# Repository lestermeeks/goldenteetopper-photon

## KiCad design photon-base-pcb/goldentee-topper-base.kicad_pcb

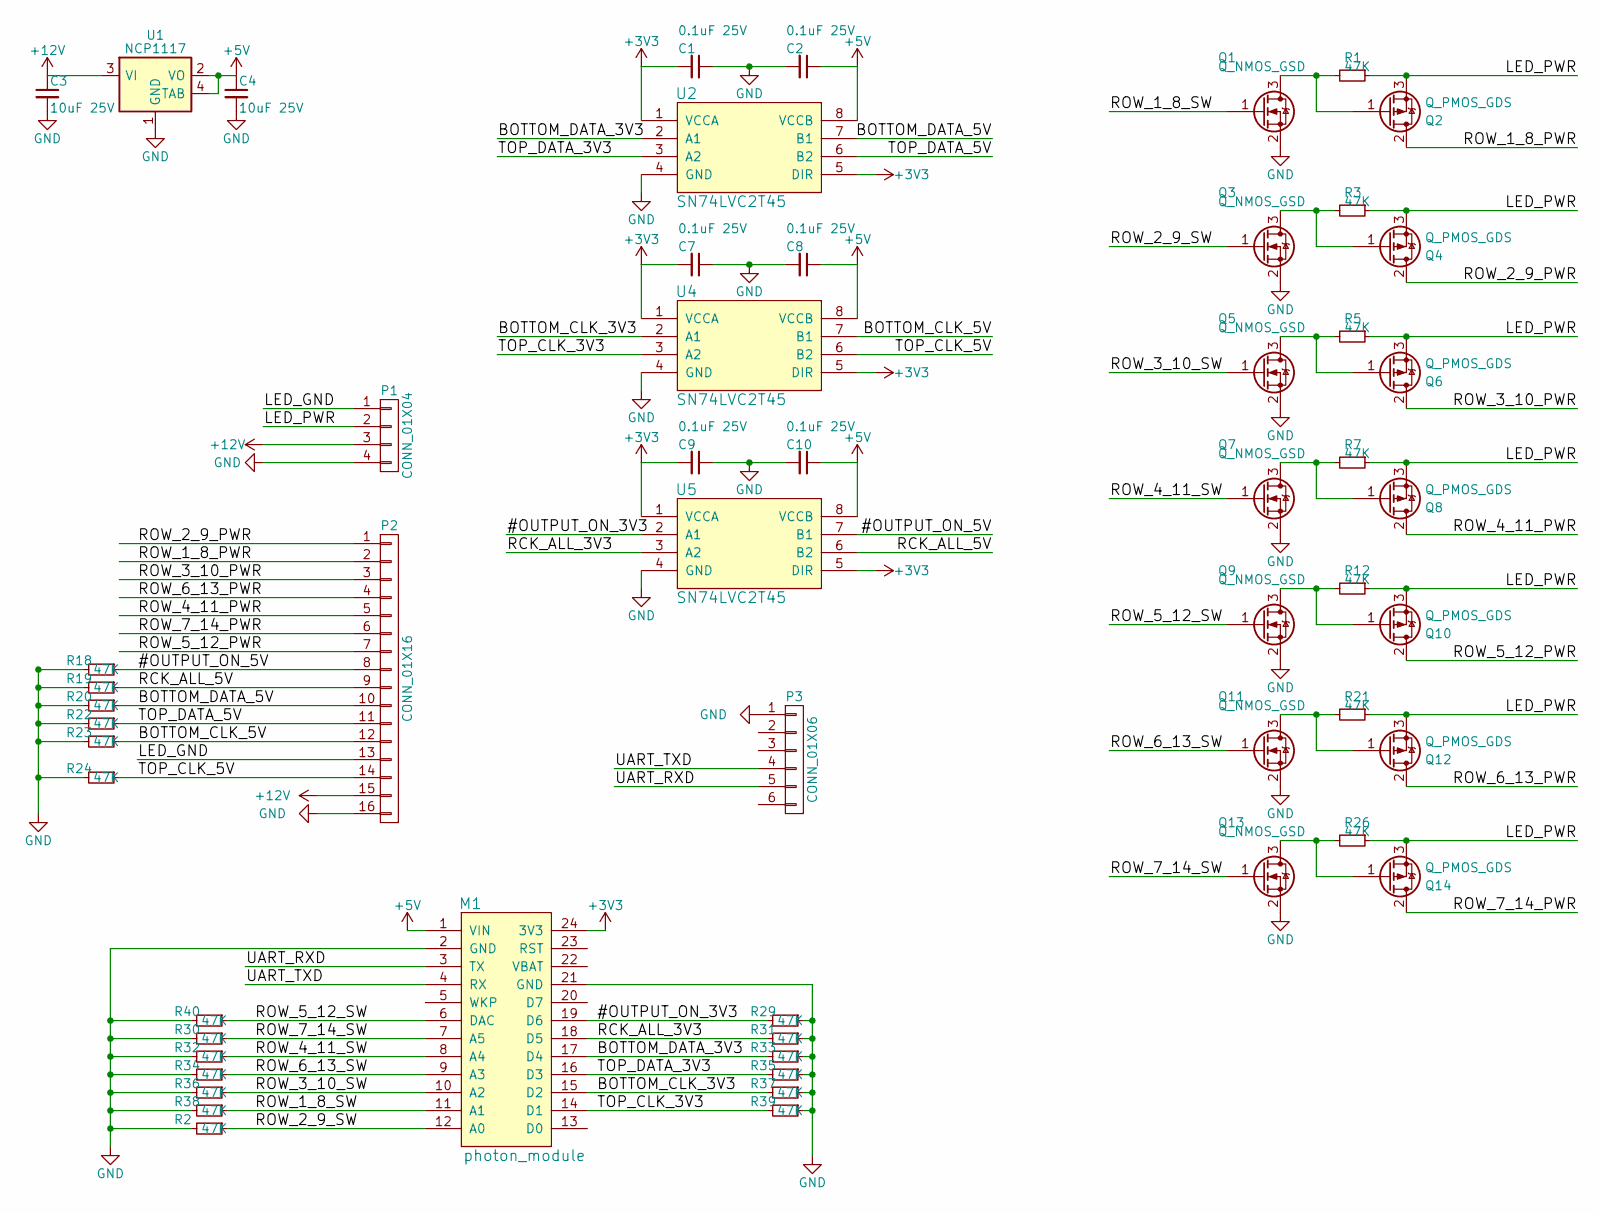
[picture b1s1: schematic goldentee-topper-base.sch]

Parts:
C1, C2, C7, C8, C9, C10: 0.1uF 25V; C_0805_HandSoldering
C3, C4: 10uF 25V; C_1210_HandSoldering
M1: photon_module; photon
P1: CONN_01X04; CONN_0.156
P2: CONN_01X16; CONN_1x16_0.156
P3: CONN_01X06; Pin_Header_Straight_1x06_Pitch2.54mm
Q1, Q3, Q5, Q7, Q9, Q11, Q13: Q_NMOS_GSD; SOT-23_Handsoldering
Q2, Q4, Q6, Q8, Q10, Q12, Q14: Q_PMOS_GDS; TO-252-2Lead
R1, R2, R3, R5, R7, R12, R18, R19, R20, R21, R22, R23, R24, R26, R29, R30, R31, R32, R33, R34, R35, R36, R37, R38, R39, R40: 47K; R_0603_HandSoldering
U1: NCP1117; SOT-223
U2, U4, U5: SN74LVC2T45; SN74LVC2T45DCTR

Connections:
+3V3: C1.2, C7.2, C9.2, M1.24 (3V3), U2.1 (VCCA), U2.5 (DIR), U4.1 (VCCA), U4.5 (DIR), U5.1 (VCCA), U5.5 (DIR)
+5V: C2.1, C4.1, C8.1, C10.1, M1.1 (VIN), U1.2 (VO), U1.4 (TAB), U2.8 (VCCB), U4.8 (VCCB), U5.8 (VCCB)
+12V: C3.1, P1.3, P2.15, U1.3 (VI)
/#OUTPUT_ON_3V3: M1.19 (D6), R29.2, U5.2 (A1)
/#OUTPUT_ON_5V: P2.8, R18.1, U5.7 (B1)
/BOTTOM_CLK_3V3: M1.15 (D2), R37.2, U4.2 (A1)
/BOTTOM_CLK_5V: P2.12, R23.1, U4.7 (B1)
/BOTTOM_DATA_3V3: M1.17 (D4), R33.2, U2.2 (A1)
/BOTTOM_DATA_5V: P2.10, R20.1, U2.7 (B1)
/LED_GND: P1.1, P2.13
/LED_PWR: P1.2, Q2.3 (S), Q4.3 (S), Q6.3 (S), Q8.3 (S), Q10.3 (S), Q12.3 (S), Q14.3 (S), R1.1, R3.1, R5.1, R7.1, R12.1, R21.1, R26.1
/RCK_ALL_3V3: M1.18 (D5), R31.2, U5.3 (A2)
/RCK_ALL_5V: P2.9, R19.1, U5.6 (B2)
/ROW_1_8_PWR: P2.2, Q2.2 (D)
/ROW_1_8_SW: M1.11 (A1), Q1.1 (G), R38.1
/ROW_2_9_PWR: P2.1, Q4.2 (D)
/ROW_2_9_SW: M1.12 (A0), Q3.1 (G), R2.1
/ROW_3_10_PWR: P2.3, Q6.2 (D)
/ROW_3_10_SW: M1.10 (A2), Q5.1 (G), R36.1
/ROW_4_11_PWR: P2.5, Q8.2 (D)
/ROW_4_11_SW: M1.8 (A4), Q7.1 (G), R32.1
/ROW_5_12_PWR: P2.7, Q10.2 (D)
/ROW_5_12_SW: M1.6 (DAC), Q9.1 (G), R40.1
/ROW_6_13_PWR: P2.4, Q12.2 (D)
/ROW_6_13_SW: M1.9 (A3), Q11.1 (G), R34.1
/ROW_7_14_PWR: P2.6, Q14.2 (D)
/ROW_7_14_SW: M1.7 (A5), Q13.1 (G), R30.1
/TOP_CLK_3V3: M1.14 (D1), R39.2, U4.3 (A2)
/TOP_CLK_5V: P2.14, R24.1, U4.6 (B2)
/TOP_DATA_3V3: M1.16 (D3), R35.2, U2.3 (A2)
/TOP_DATA_5V: P2.11, R22.1, U2.6 (B2)
/UART_RXD: M1.3 (TX), P3.5
/UART_TXD: M1.4 (RX), P3.4
GND: C1.1, C2.2, C3.2, C4.2, C7.1, C8.2, C9.1, C10.2, M1.2 (GND), M1.21 (GND), P1.4, P2.16, P3.1, Q1.2 (S), Q3.2 (S), Q5.2 (S), Q7.2 (S), Q9.2 (S), Q11.2 (S), Q13.2 (S), R2.2, R18.2, R19.2, R20.2, R22.2, R23.2, R24.2, R29.1, R30.2, R31.1, R32.2, R33.1, R34.2, R35.1, R36.2, R37.1, R38.2, R39.1, R40.2, U1.1 (GND), U2.4 (GND), U4.4 (GND), U5.4 (GND)
unnamed: Q1.3 (D), Q2.1 (G), R1.2
unnamed: Q3.3 (D), Q4.1 (G), R3.2
unnamed: Q5.3 (D), Q6.1 (G), R5.2
unnamed: Q7.3 (D), Q8.1 (G), R7.2
unnamed: Q9.3 (D), Q10.1 (G), R12.2
unnamed: Q11.3 (D), Q12.1 (G), R21.2
unnamed: Q13.3 (D), Q14.1 (G), R26.2

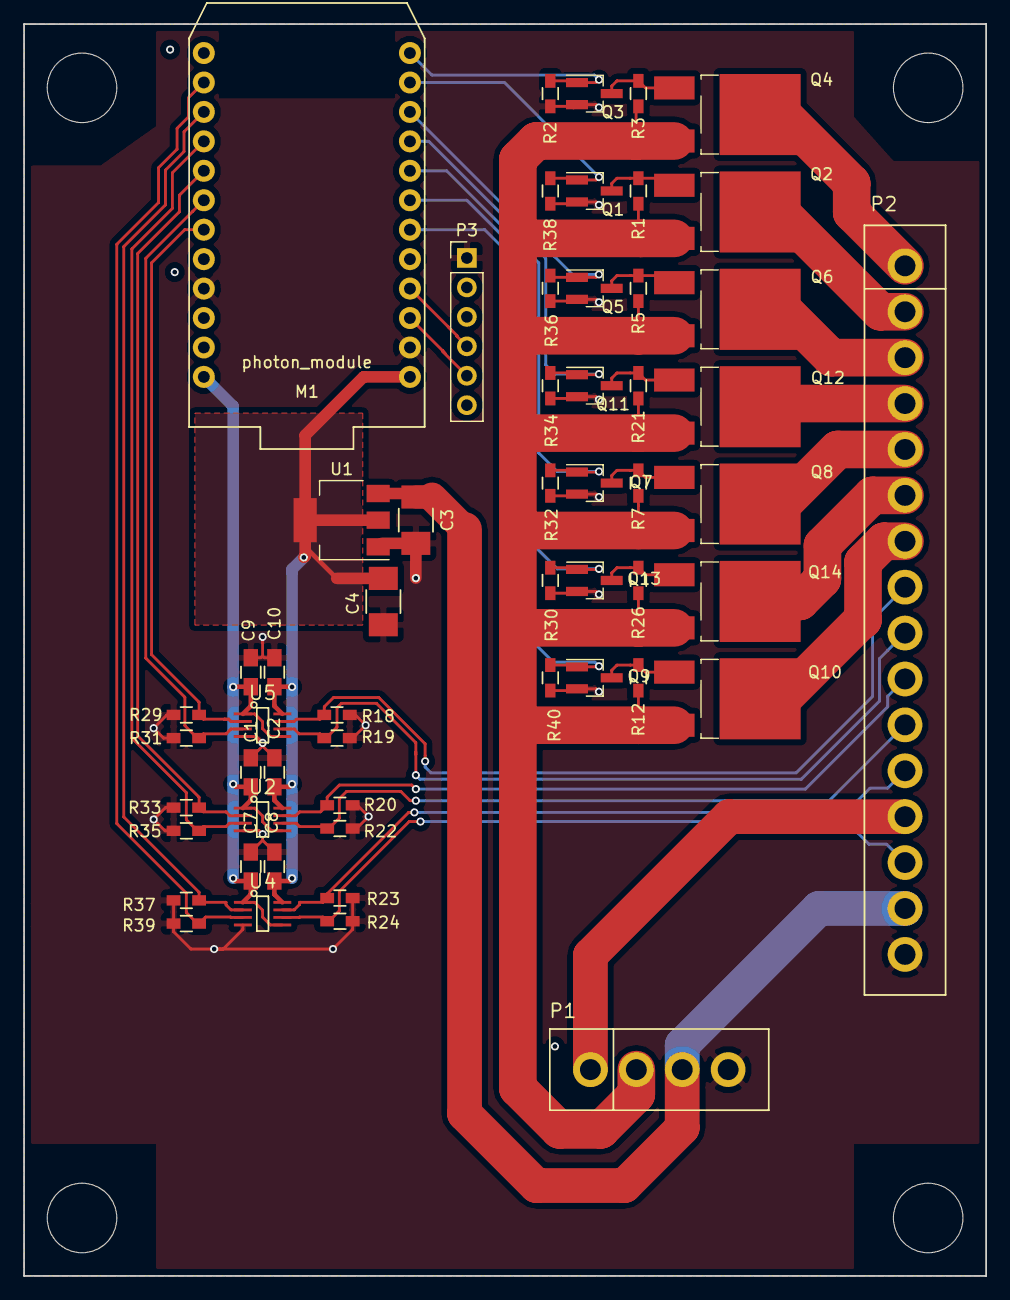
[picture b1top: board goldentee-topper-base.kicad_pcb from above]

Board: 2 copper layers, 83.0 x 108.0 mm, 56 parts (0 on the bottom side), 41 nets.

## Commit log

2017-03-07 initial
2017-03-07 first concept layout
2017-03-08 Small Square pcb, silk yet to be arranged.
2017-03-08 V3 Release
2017-03-08 bom work
2017-03-10 fixed sideways nfets, relayed out the area around the new FET configuration. BOM updates for all the initial parts. BOM reflects the fixed NFET pinout.
2017-03-10 level shifter footprint update
2018-02-07 pre level shifter and nchan fix.
